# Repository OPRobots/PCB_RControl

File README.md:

# PCB_RControl
PCB para el control de barcos y coches solares de la competición "regata solar Marine Instruments"

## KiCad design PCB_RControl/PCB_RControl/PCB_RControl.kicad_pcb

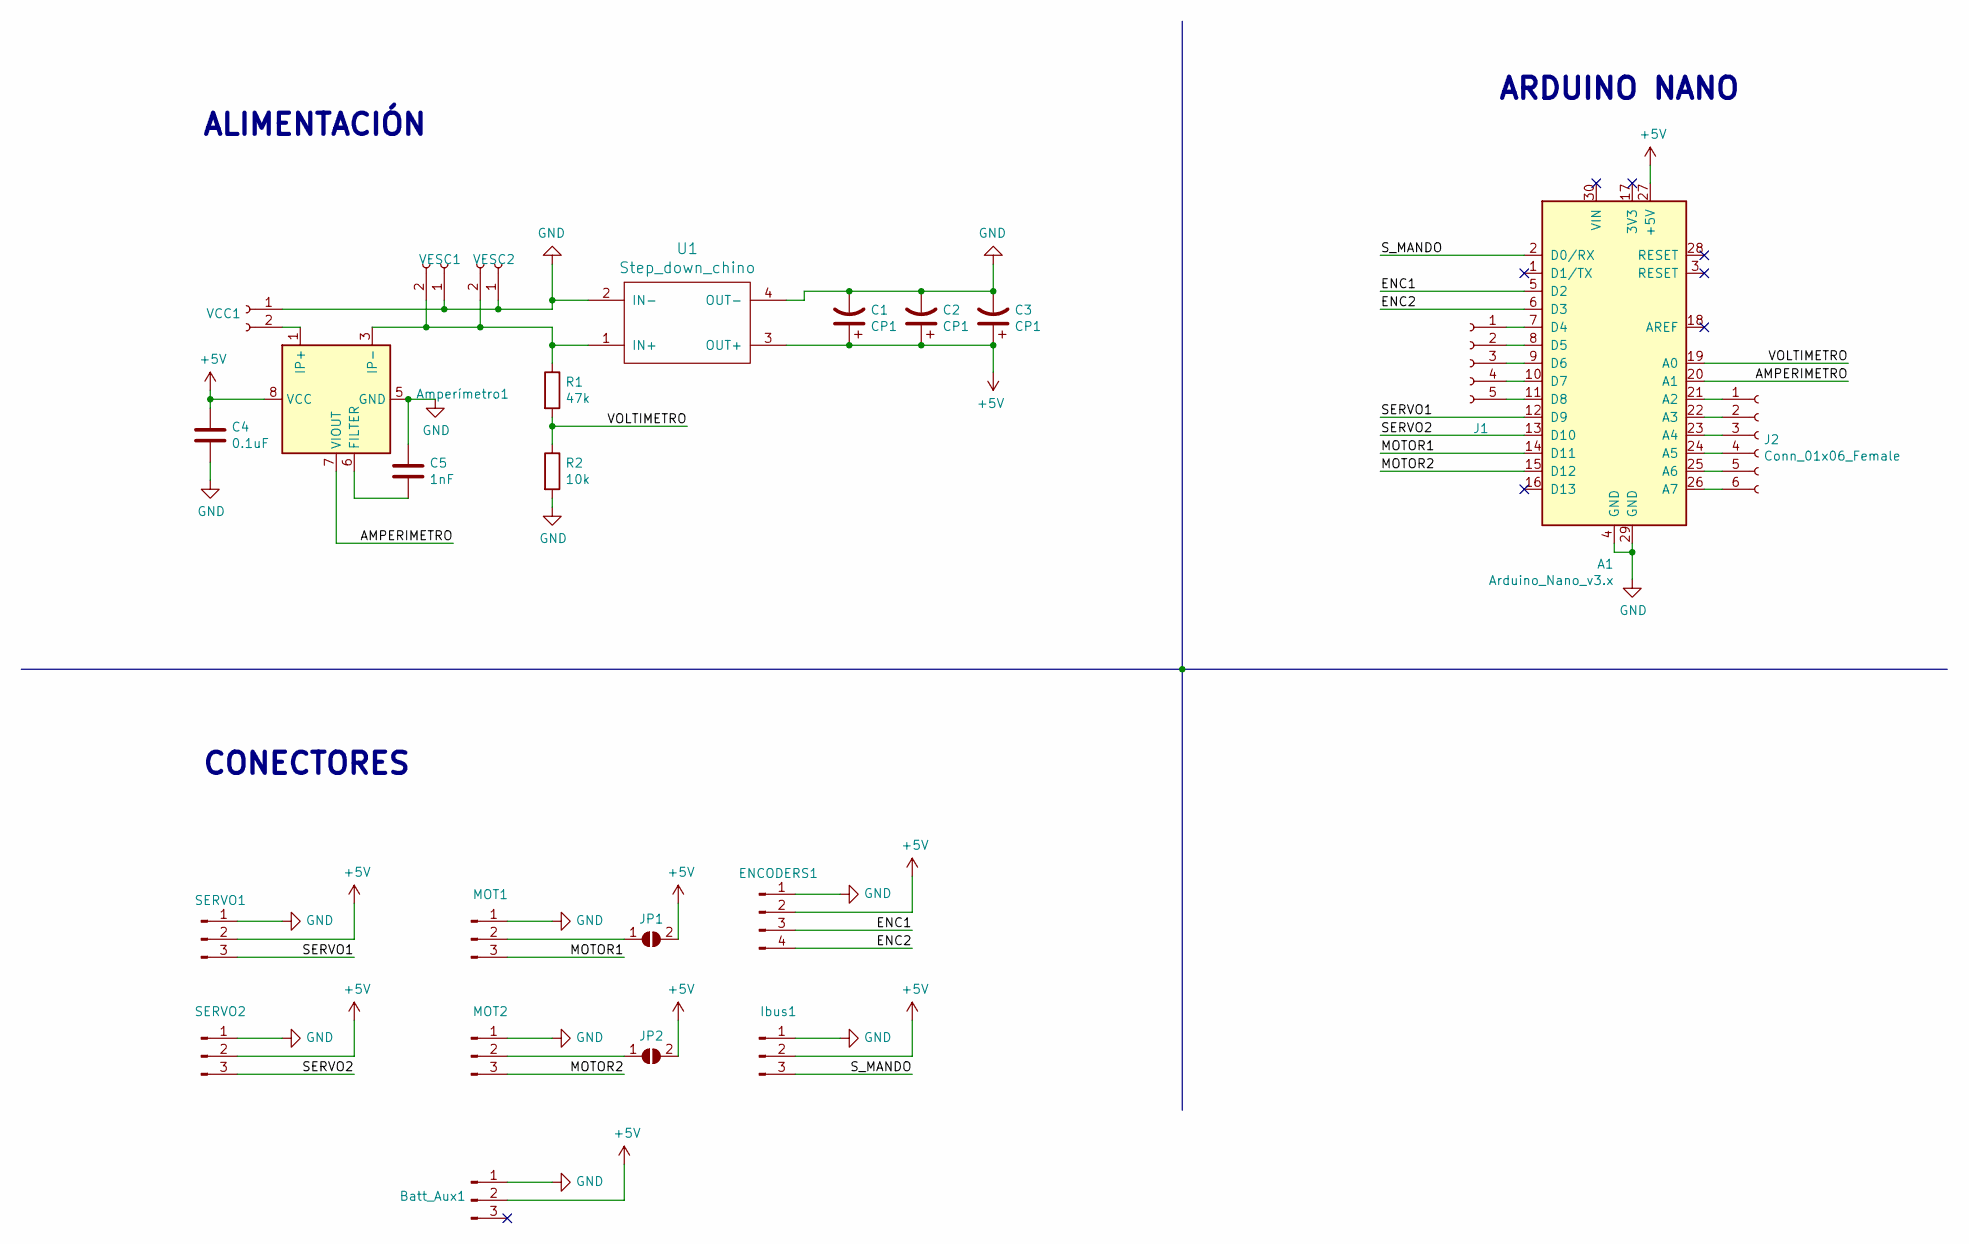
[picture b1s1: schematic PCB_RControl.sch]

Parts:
A1: Arduino_Nano_v3.x; Arduino_Nano
Amperímetro1: ACS712xLCTR-20A; SOIC-8_3.9x4.9mm_P1.27mm
Batt_Aux1: Conn_01x03_Male; PinHeader_1x03_P2.54mm_Vertical
C1, C2, C3: CP1; CP_Radial_D12.5mm_P5.00mm
C4: 0.1uF; C_0805_2012Metric_Pad1.15x1.40mm_HandSolder
C5: 1nF; C_0805_2012Metric_Pad1.15x1.40mm_HandSolder
ENCODERS1: Conn_01x04_Male; PinHeader_1x04_P2.54mm_Vertical
Ibus1: Conn_01x03_Male; PinHeader_1x03_P2.54mm_Vertical
J1: Conn_01x05_Female; PinHeader_1x05_P2.54mm_Vertical
J2: Conn_01x06_Female; PinHeader_1x06_P2.54mm_Vertical
JP1, JP2: SolderJumper_2_Open; SolderJumper-2_P1.3mm_Open_TrianglePad1.0x1.5mm
MOT1, MOT2: Conn_01x03_Male; PinHeader_1x03_P2.54mm_Vertical
R1: 47k; R_0805_2012Metric_Pad1.15x1.40mm_HandSolder
R2: 10k; R_0805_2012Metric_Pad1.15x1.40mm_HandSolder
SERVO1, SERVO2: Conn_01x03_Male; PinHeader_1x03_P2.54mm_Vertical
U1: Step_down_chino; Mini360
VCC1: Conn_01x02_Female; PinHeader_1x02_P2.54mm_Vertical
VESC1, VESC2: Conn_01x02_Female; PinHeader_1x02_P2.54mm_Vertical

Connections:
+5V: A1.27 (+5V), Amperímetro1.8 (VCC), Batt_Aux1.2, C1.1, C2.1, C3.1, C4.1, ENCODERS1.2, Ibus1.2, JP1.2 (B), JP2.2 (B), SERVO1.2, SERVO2.2, U1.3 (OUT+)
/AMPERIMETRO: A1.20 (A1), Amperímetro1.7 (VIOUT)
/ENC1: A1.5 (D2), ENCODERS1.3
/ENC2: A1.6 (D3), ENCODERS1.4
/MOTOR1: A1.14 (D11), MOT1.3
/MOTOR2: A1.15 (D12), MOT2.3
/SERVO1: A1.12 (D9), SERVO1.3
/SERVO2: A1.13 (D10), SERVO2.3
/S_MANDO: A1.2 (D0/RX), Ibus1.3
/VOLTIMETRO: A1.19 (A0), R1.2, R2.1
GND: A1.4 (GND), A1.29 (GND), Amperímetro1.5 (GND), Batt_Aux1.1, C1.2, C2.2, C3.2, C4.2, C5.1, ENCODERS1.1, Ibus1.1, MOT1.1, MOT2.1, R2.2, SERVO1.1, SERVO2.1, U1.2 (IN-), U1.4 (OUT-), VCC1.1, VESC1.1, VESC2.1; also elsewhere on the board
unnamed: A1.7 (D4), J1.1
unnamed: A1.8 (D5), J1.2
unnamed: A1.9 (D6), J1.3
unnamed: A1.10 (D7), J1.4
unnamed: A1.11 (D8), J1.5
unnamed: A1.21 (A2), J2.1
unnamed: A1.22 (A3), J2.2
unnamed: A1.23 (A4), J2.3
unnamed: A1.24 (A5), J2.4
unnamed: A1.25 (A6), J2.5
unnamed: A1.26 (A7), J2.6
unnamed 29: Amperímetro1.1 (IP+), Amperímetro1.2 (IP+), VCC1.2; also elsewhere on the board
unnamed: Amperímetro1.3 (IP-), Amperímetro1.4 (IP-), R1.1, U1.1 (IN+), VESC1.2, VESC2.2
unnamed: Amperímetro1.6 (FILTER), C5.2
unnamed: JP1.1 (A), MOT1.2
unnamed: JP2.1 (A), MOT2.2

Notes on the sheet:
ARDUINO NANO
ALIMENTACIÓN
CONECTORES

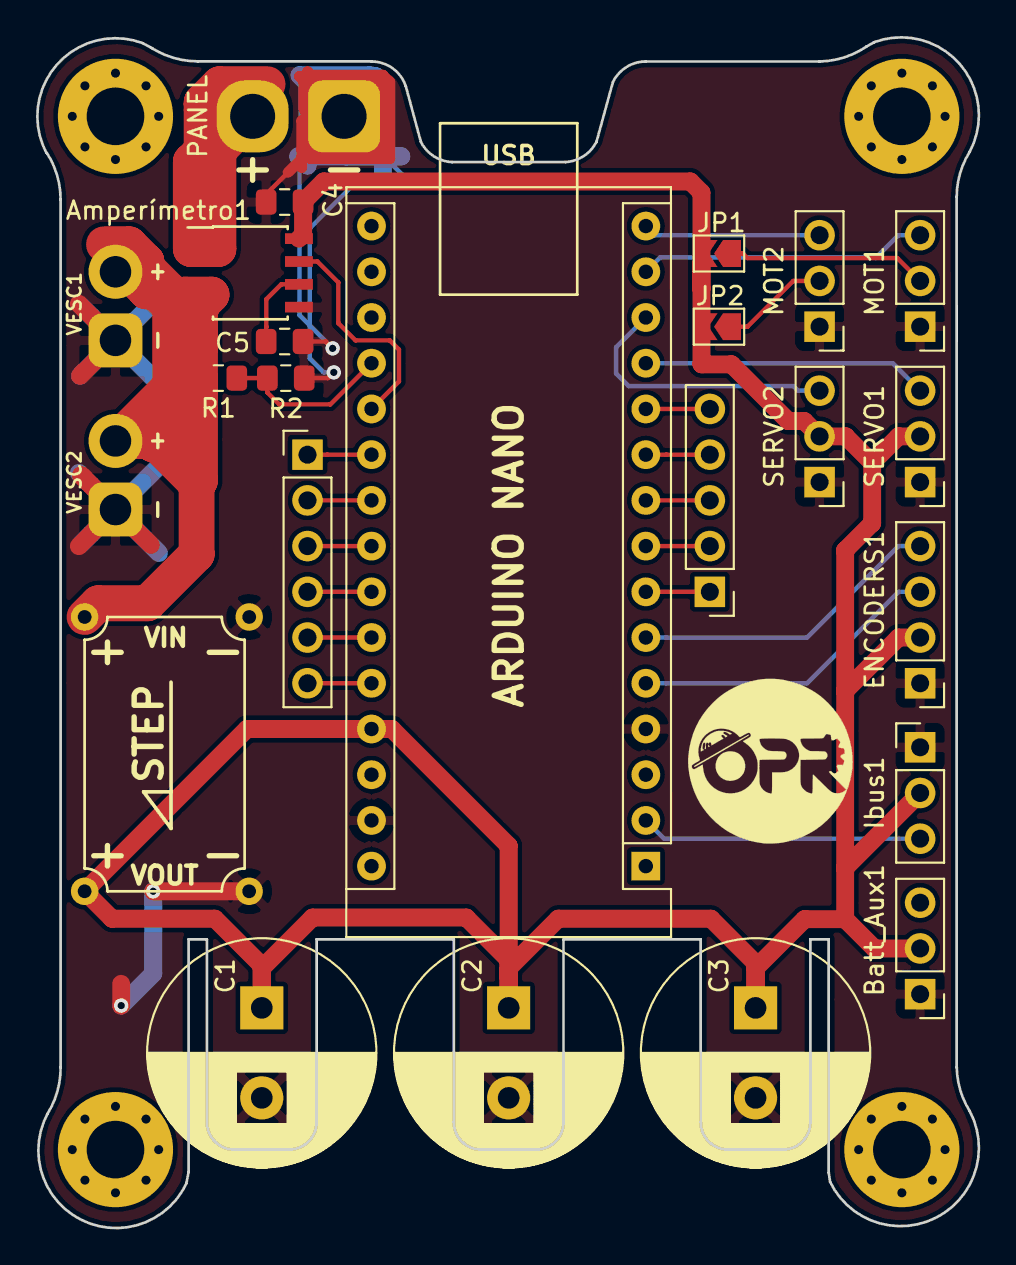
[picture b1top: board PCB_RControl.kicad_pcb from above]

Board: 2 copper layers, 52.3 x 66.1 mm, 24 parts (0 on the bottom side), 27 nets.

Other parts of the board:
PANEL: Conn_01x02_Female; PinHeader_1x02_P2.54mm_Vertical

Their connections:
GND: PANEL.1; also elsewhere on the board
unnamed 29: PANEL.2; also elsewhere on the board

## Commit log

2019-06-27 Subida de archivos
2019-06-27 Adjuntar imagen en el readme
2019-06-27 Create LICENSE
